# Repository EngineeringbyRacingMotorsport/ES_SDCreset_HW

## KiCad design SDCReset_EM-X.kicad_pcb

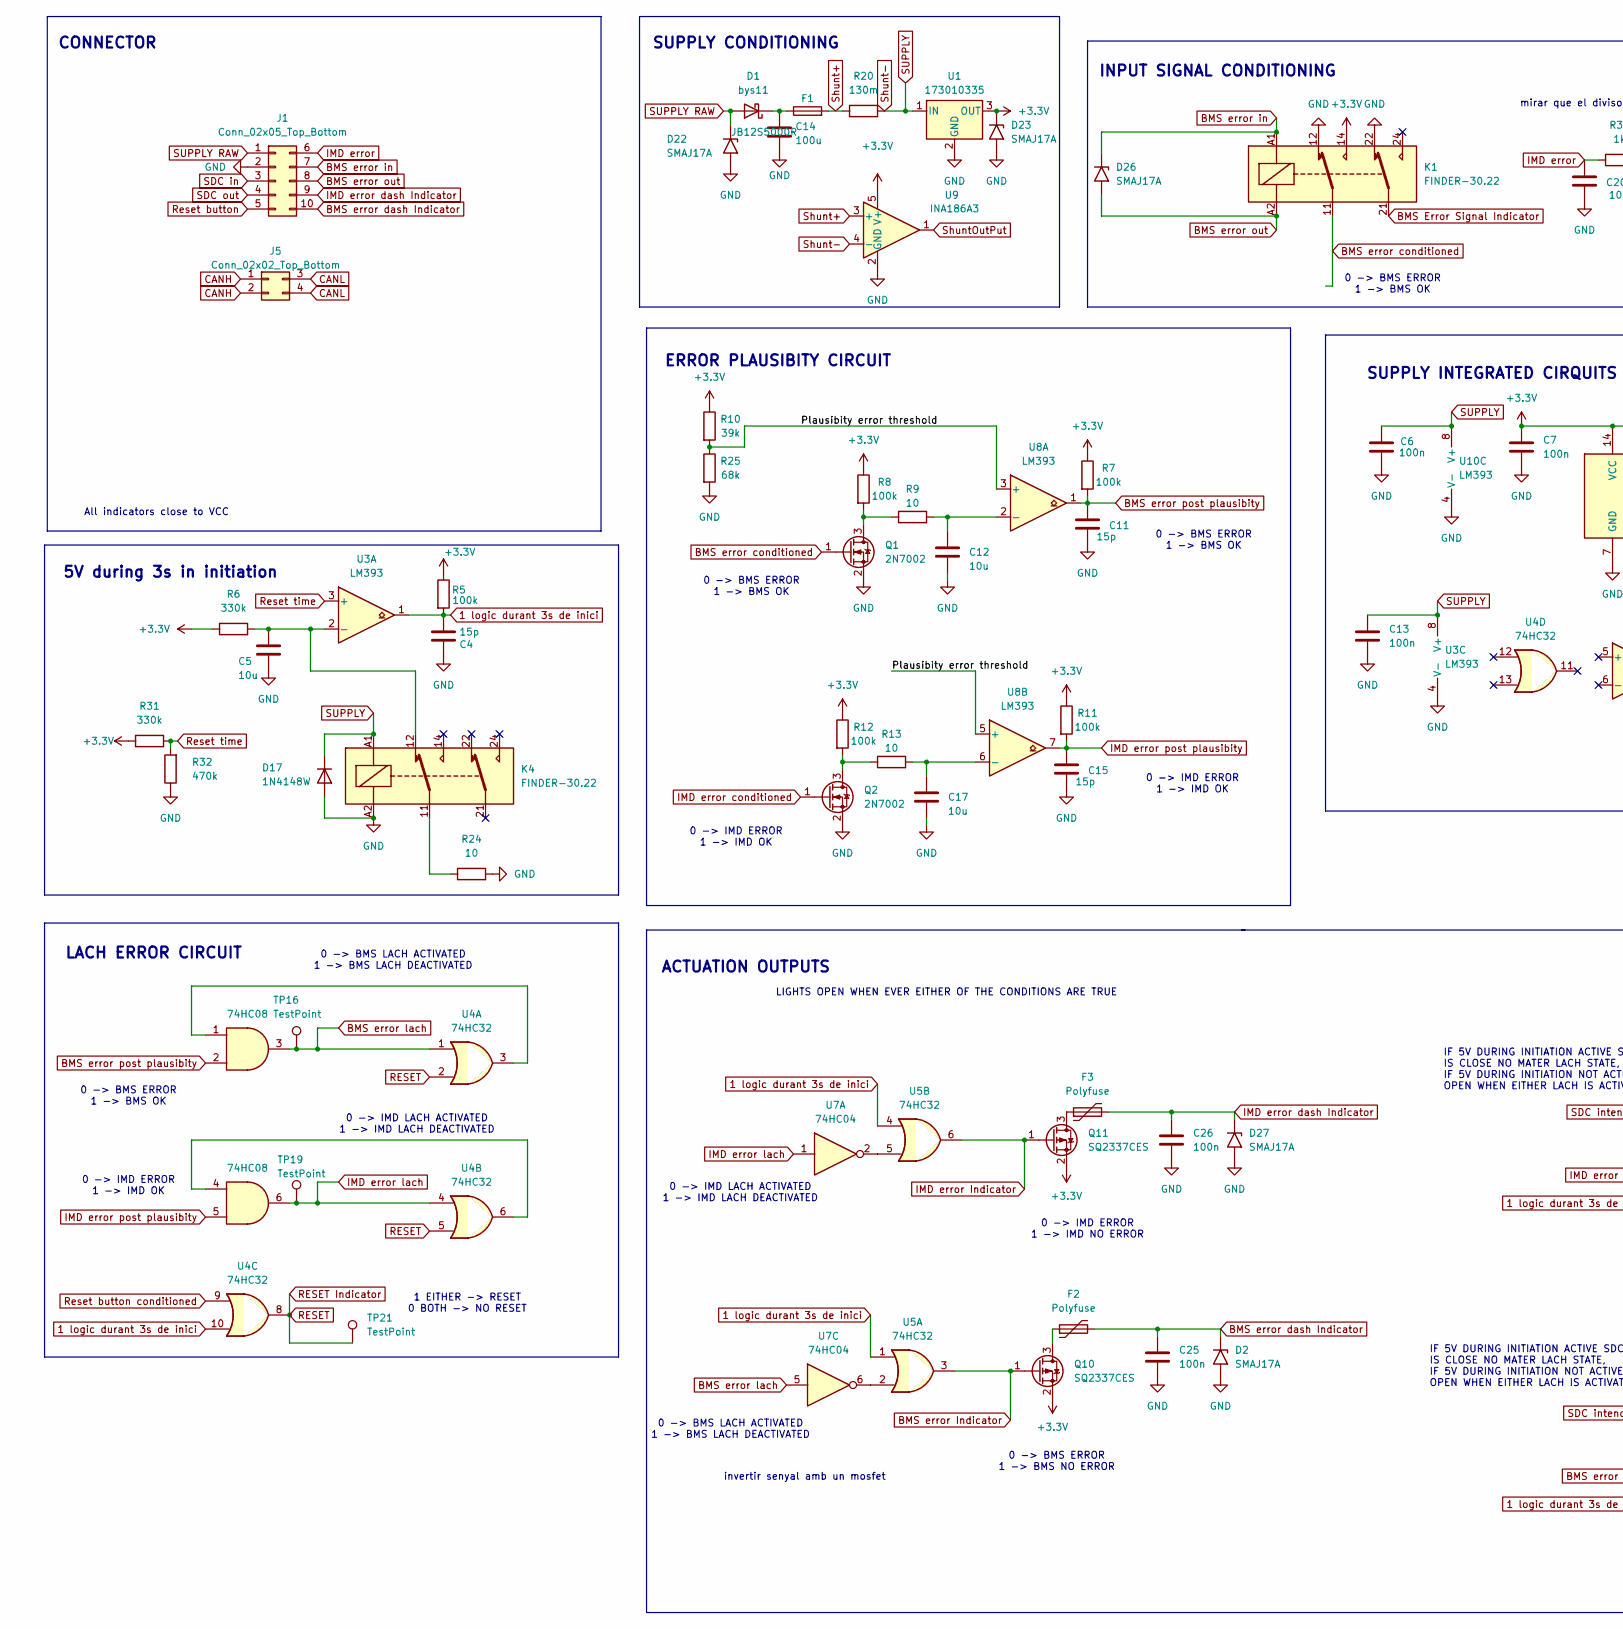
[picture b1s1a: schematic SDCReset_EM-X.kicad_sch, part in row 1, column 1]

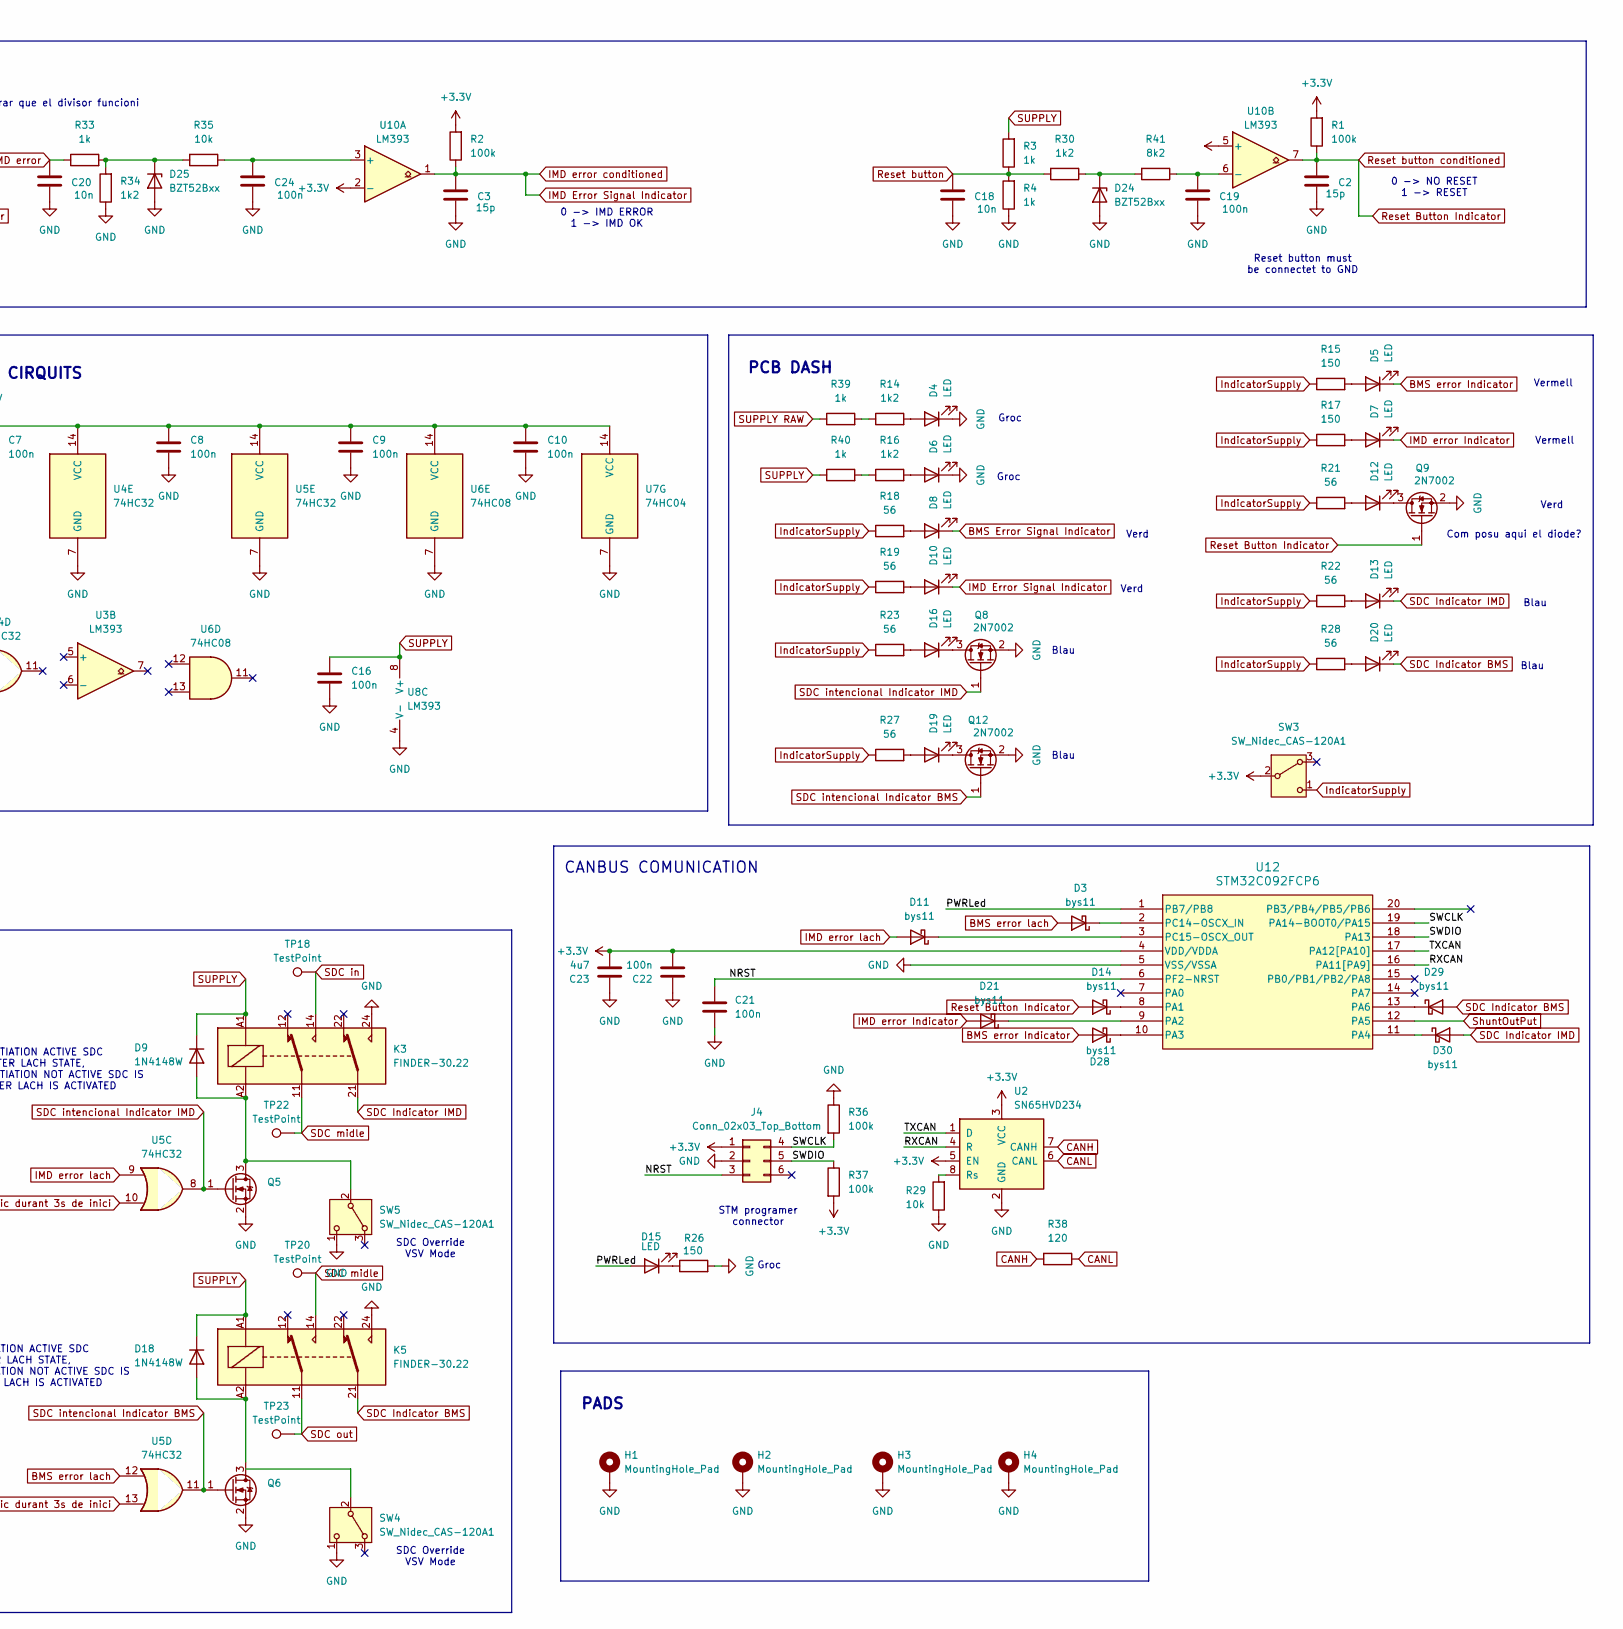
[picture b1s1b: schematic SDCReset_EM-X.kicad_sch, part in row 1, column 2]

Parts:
C2, C3, C4, C11, C15: 15p; C_0603_1608Metric
C5, C12, C17: 10u; C_0603_1608Metric
C6, C7, C8, C9, C10, C13, C16, C19, C21, C22, C24, C25, C26: 100n; C_0603_1608Metric
C14: 100u; CP_Elec_10x10
C18, C20: 10n; C_0603_1608Metric
C23: 4u7; C_0603_1608Metric
D1: bys11; D_SMA
D2, D22, D23, D26, D27: SMAJ17A; D_SMB
D3, D11, D14, D21, D28, D29, D30: bys11; D_SOD-523
D4, D5, D6, D7, D8, D10, D12, D13, D15, D16, D19, D20: LED; LED_0603_1608Metric
D9, D17, D18: 1N4148W; D_SOD-123
D24, D25: BZT52Bxx; D_SOD-123F
F1: JB12S5000R; Fuse_1206_3216Metric
F2, F3: Polyfuse; Fuse_0603_1608Metric
H1, H2, H3, H4: MountingHole_Pad; MountingHole_3.5mm_Pad_Via
J1: Conn_02x05_Top_Bottom; Molex_Nano-Fit_105314-xx10_2x05_P2.50mm_Horizontal
J4: Conn_02x03_Top_Bottom; PinSocket_2x03_P1.27mm_Vertical_SMD
J5: Conn_02x02_Top_Bottom; Molex_Nano-Fit_105314-xx04_2x02_P2.50mm_Horizontal
K1, K3, K4, K5: FINDER-30.22; Relay_DPDT_Finder_30.22
Q1, Q2, Q5, Q6, Q8, Q9, Q12: 2N7002; SOT-23
Q10, Q11: SQ2337CES; SOT-23
R1, R2, R5, R7, R8, R11, R12, R36, R37: 100k; R_0603_1608Metric
R3, R4, R33: 1k; R_0603_1608Metric
R6, R31: 330k; R_0603_1608Metric
R9, R13, R24: 10; R_0603_1608Metric
R10: 39k; R_0603_1608Metric
R14, R16: 1k2; R_1206_3216Metric
R15, R17, R26: 150; R_0603_1608Metric
R18, R19, R21, R22, R23, R27, R28: 56; R_0603_1608Metric
R20: 130m; R_0603_1608Metric
R25: 68k; R_0603_1608Metric
R29, R35: 10k; R_0603_1608Metric
R30, R34: 1k2; R_0603_1608Metric
R32: 470k; R_0603_1608Metric
R38: 120; R_0603_1608Metric
R39, R40: 1k; R_1206_3216Metric
R41: 8k2; R_0603_1608Metric
SW3, SW4, SW5: SW_Nidec_CAS-120A1; Nidec_Copal_CAS-120A
TP16, TP18, TP19, TP20, TP21, TP22, TP23: TestPoint; TestPoint_Pad_D1.0mm
U1: 173010335; Converter_DCDC_RECOM_R-78E-0.5_THT
U2: SN65HVD234; SOIC-8_3.9x4.9mm_P1.27mm
U3, U8, U10: LM393; TSSOP-8_4.4x3mm_P0.65mm
U4, U5: 74HC32; TSSOP-14_4.4x5mm_P0.65mm
U6: 74HC08; TSSOP-14_4.4x5mm_P0.65mm
U7: 74HC04; TSSOP-14_4.4x5mm_P0.65mm
U9: INA186A3; SOT-23-5
U12: STM32C092FCP6; TSSOP-20_4.4x6.5mm_P0.65mm

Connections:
1 logic durant 3s de inici: C4.1, R5.2, U3.1, U4.10, U5.1, U5.4, U5.10, U5.13
+3.3V: C7.1, C8.1, C9.1, C10.1, C22.2, C23.2, D23.1 (A1), J4.1, K1.14, Q10.2 (S), Q11.2 (S), R1.2, R2.2, R5.1, R6.1, R7.1, R8.1, R10.1, R11.1, R12.1, R31.1, R37.2, SW3.2 (B), U1.3 (OUT), U2.3 (VCC), U2.5 (EN), U4.14 (VCC), U5.14 (VCC), U6.14 (VCC), U7.14 (VCC), U9.5 (V+), U10.2 (-), U10.5 (+), U12.4 (VDD/VDDA)
/NRST: C21.1, J4.3, U12.6 (PF2-NRST)
/PWRLed: D15.2 (A), U12.1 (PB7/PB8)
/Plausibity error threshold: R10.2, R25.1, U8.3 (+), U8.5 (+)
/RXCAN: U2.4 (R), U12.16 (PA11[PA9])
/SWCLK: J4.4, R36.2, U12.19 (PA14-BOOT0/PA15)
/SWDIO: J4.5, R37.1, U12.18 (PA13)
/TXCAN: U2.1 (D), U12.17 (PA12[PA10])
BMS Error Signal Indicator: D8.1 (K), K1.21
BMS error Indicator: D5.1 (K), D28.2 (A), Q10.1 (G), U5.3
BMS error conditioned: K1.11, Q1.1 (G)
BMS error dash Indicator: C25.1, D2.1 (A1), F2.2, J1.10
BMS error in: D26.1 (A1), J1.7, K1.A1
BMS error lach: D3.2 (A), TP16.1 (1_1), U4.1, U5.12, U6.3, U7.5
BMS error out: D26.2 (A2), J1.8, K1.A2
BMS error post plausibity: C11.1, R7.2, U6.2, U8.1
CANH: J5.1, J5.2, R38.2, U2.7 (CANH)
CANL: J5.3, J5.4, R38.1, U2.6 (CANL)
GND: C2.2, C3.2, C4.2, C5.2, C6.2, C7.2, C8.2, C9.2, C10.2, C11.2, C12.2, C13.2, C14.2, C15.2, C16.2, C17.2, C18.2, C19.2, C20.2, C21.2, C22.1, C23.1, C24.2, C25.2, C26.2, D2.2 (A2), D4.1 (K), D6.1 (K), D17.2 (A), D22.2 (A2), D23.2 (A2), D24.2 (A), D25.2 (A), D27.2 (A2), H1.1 (1_1), H2.1 (1_1), H3.1 (1_1), H4.1 (1_1), J1.2, J4.2, K1.12, K1.22, K3.24, K4.A2, K5.24, Q1.2 (S), Q2.2 (S), Q5.2 (S), Q6.2 (S), Q8.2 (S), Q9.2 (S), Q12.2 (S), R4.1, R24.2, R25.2, R26.2, R29.1, R32.1, R34.1, R36.1, SW4.1 (C_1), SW5.1 (C), U1.2 (GND), U2.2 (GND), U3.4 (V-), U4.7 (GND), U5.7 (GND), U6.7 (GND), U7.7 (GND), U8.4 (V-), U9.2 (GND), U10.4 (V-), U12.5 (VSS/VSSA)
IMD Error Signal Indicator: C3.1, D10.1 (K), Q2.1 (G), R2.1, U10.1
IMD error: C20.1, J1.6, R33.1
IMD error Indicator: D7.1 (K), D21.2 (A), Q11.1 (G), U5.6
IMD error dash Indicator: C26.1, D27.1 (A1), F3.2, J1.9
IMD error lach: D11.2 (A), TP19.1 (1_1), U4.4, U5.9, U6.6, U7.1
IMD error post plausibity: C15.1, R11.2, U6.5, U8.7
IndicatorSupply: R15.1, R17.1, R18.1, R19.1, R21.1, R22.1, R23.1, R27.1, R28.1, SW3.1 (C)
unnamed: C14.1, D1.1 (K), F1.1
unnamed: D3.1 (K), U12.2 (PC14-OSCX_IN)
unnamed: D4.2 (A), R14.2
unnamed: D5.2 (A), R15.2
unnamed: D6.2 (A), R16.2
unnamed: D7.2 (A), R17.2
unnamed: D8.2 (A), R18.2
unnamed: D9.2 (A), K3.A2, Q5.3 (D), SW5.2 (B)
unnamed: D10.2 (A), R19.2
unnamed: D11.1 (K), U12.3 (PC15-OSCX_OUT)
unnamed: D12.2 (A), R21.2
unnamed: D12.1 (K), Q9.3 (D)
unnamed: D13.2 (A), R22.2
unnamed: D14.1 (K), U12.8 (PA1)
unnamed: D15.1 (K), R26.1
unnamed: D16.2 (A), R23.2
unnamed: D16.1 (K), Q8.3 (D)
unnamed: D18.2 (A), K5.A2, Q6.3 (D)
unnamed: D19.2 (A), R27.2
unnamed: D19.1 (K), Q12.3 (D)
unnamed: D20.2 (A), R28.2
unnamed: D21.1 (K), U12.9 (PA2)
unnamed: D24.1 (K), R30.1, R41.2
unnamed: D25.1 (K), R33.2, R34.2, R35.2
unnamed: D28.1 (K), U12.10 (PA3)
unnamed: D29.1 (K), U12.13 (PA6)
unnamed: D30.1 (K), U12.11 (PA4)
unnamed: K4.11, R24.1
unnamed: Q1.3 (D), R8.2, R9.1
unnamed: Q2.3 (D), R12.2, R13.1
unnamed: F2.1, Q10.3 (D)
unnamed: F3.1, Q11.3 (D)
unnamed: R14.1, R39.2
unnamed: R16.1, R40.2
unnamed: R29.2, U2.8 (Rs)
unnamed: C5.1, K4.12, R6.2, U3.2 (-)
unnamed: U4.3, U6.1
unnamed: U4.6, U6.4
unnamed: U5.2, U7.6
unnamed: U5.5, U7.2
unnamed: C12.1, R9.2, U8.2 (-)
unnamed: C17.1, R13.2, U8.6 (-)
unnamed: C24.1, R35.1, U10.3 (+)
unnamed: C19.1, R41.1, U10.6 (-)
RESET: TP21.1 (1_1), U4.2, U4.5, U4.8
Reset Button Indicator: C2.1, D14.2 (A), Q9.1 (G), R1.1, U4.9, U10.7
Reset button: C18.1, J1.5, R3.1, R4.2, R30.2
Reset time: R31.2, R32.2, U3.3 (+)
SDC Indicator BMS: D20.1 (K), D29.2 (A), K5.21
SDC Indicator IMD: D13.1 (K), D30.2 (A), K3.21
SDC in: J1.3, K3.14, TP18.1 (1_1)
SDC intencional Indicator BMS: Q6.1 (G), Q12.1 (G), U5.11
SDC intencional Indicator IMD: Q5.1 (G), Q8.1 (G), U5.8
SDC midle: K3.11, K5.14, TP20.1 (1_1), TP22.1 (1_1)
SDC out: J1.4, K5.11, TP23.1 (1_1)
SUPPLY: C6.1, C13.1, C16.1, D9.1 (K), D17.1 (K), D18.1 (K), K3.A1, K4.A1, K5.A1, R3.2, R20.2, R40.1, U1.1 (IN), U3.8 (V+), U8.8 (V+), U9.4 (-), U10.8 (V+)
SUPPLY RAW: D1.2 (A), D22.1 (A1), J1.1, R39.1
Shunt+: F1.2, R20.1, U9.3 (+)
ShuntOutPut: U9.1, U12.12 (PA5)

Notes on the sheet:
CANBUS COMUNICATION
Verd
0 -> IMD ERROR 1 -> IMD OK
mirar que el divisor funcioni
0 -> BMS LACH ACTIVATED 1 -> BMS LACH DEACTIVATED
0 -> NO RESET 1 -> RESET
Groc
Blau
0 -> BMS ERROR 1 -> BMS OK
STM programer connector
Vermell
0 -> IMD LACH ACTIVATED 1 -> IMD LACH DEACTIVATED
SUPPLY CONDITIONING
LACH ERROR CIRCUIT
LIGHTS OPEN WHEN EVER EITHER OF THE CONDITIONS ARE TRUE
invertir senyal amb un mosfet
IF 5V DURING INITIATION ACTIVE SDC IS CLOSE NO MATER LACH STATE, IF 5V DURING INITIATION NOT ACTIVE SDC IS OPEN WHEN EITHER LACH IS ACTIVATED
PADS
SUPPLY INTEGRATED CIRQUITS
0 -> IMD ERROR 1 -> IMD NO ERROR
Com posu aqui el diode?
PCB DASH
ERROR PLAUSIBITY CIRCUIT
0 -> BMS ERROR 1 -> BMS NO ERROR
1 EITHER -> RESET 0 BOTH -> NO RESET
INPUT SIGNAL CONDITIONING
5V during 3s in initiation
All indicators close to VCC
SDC Override VSV Mode
CONNECTOR
ACTUATION OUTPUTS
Reset button must be connectet to GND

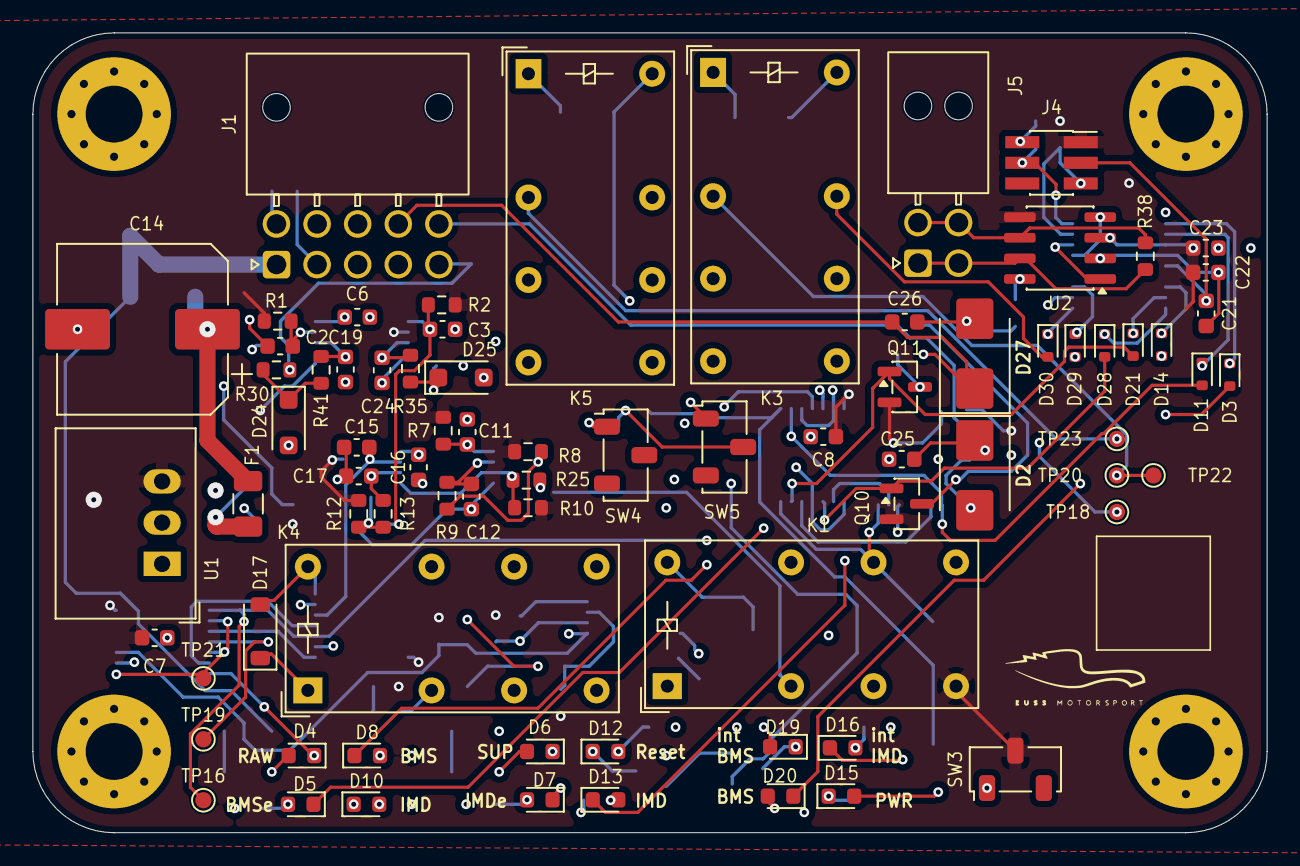
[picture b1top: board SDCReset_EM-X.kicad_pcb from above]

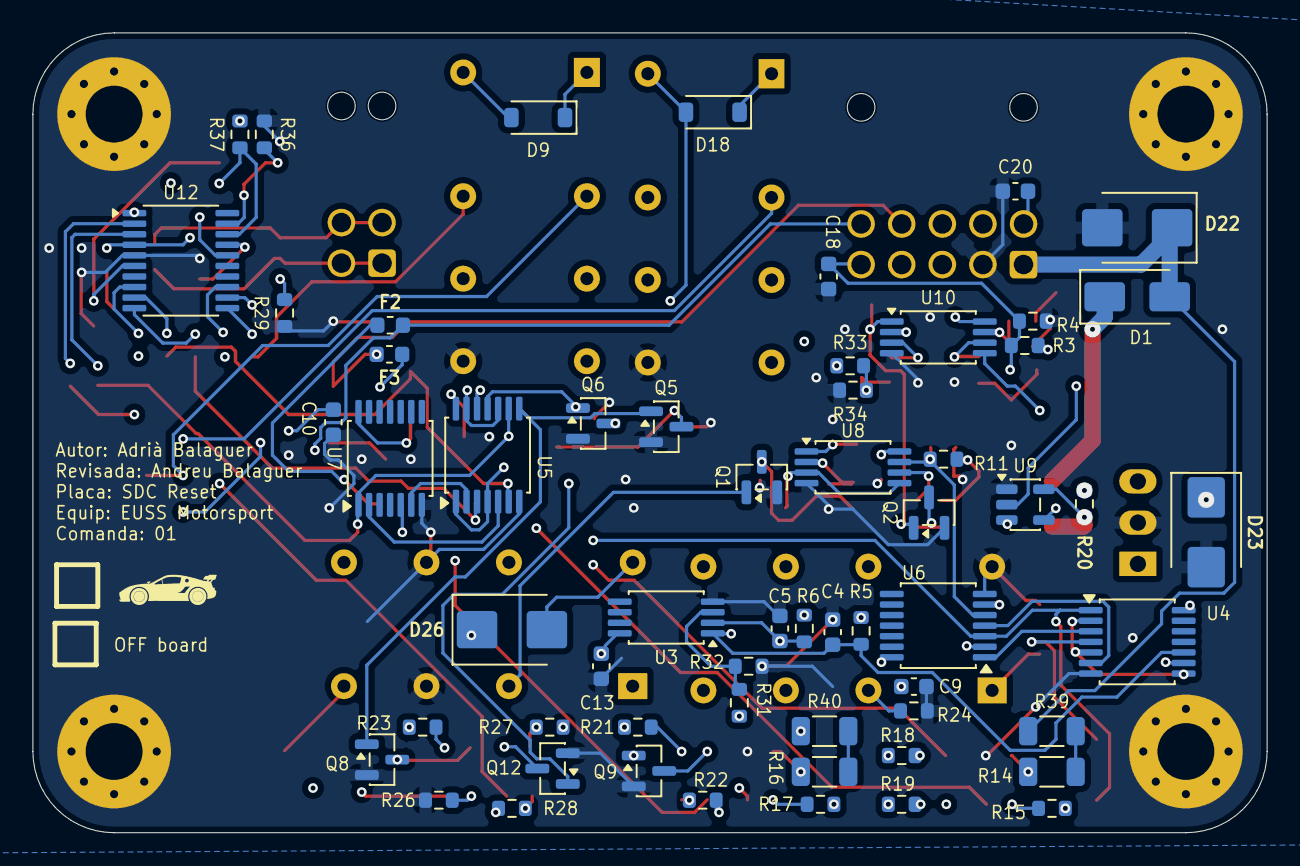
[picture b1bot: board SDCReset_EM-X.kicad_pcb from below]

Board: 4 copper layers, 76.0 x 49.2 mm, 140 parts (59 on the bottom side), 86 nets.

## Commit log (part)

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2026-03-24 - Commit inicial. - Primera versió del EM-06 enviada a fabricar.
